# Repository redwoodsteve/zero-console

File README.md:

# Lua Console
A console which uses the RPi Zero 2 W
## setup
-Make sure to set the username and password of your pi lite image to "pi"!
-cd into `software`, and run `sudo ./setup.sh`. You should also probably turn on auto login.
## software
The folder which houses the software, such as the home screen. Basically all of this code is in C++ for a low memory footprint and stuff.<br>
**Development:**<br>
For `launcher`:
 - For windows, install MinGW64, open the UCRT64 console, CD into the launcher directory and use `make`
 - For linux, CD into the launcher directory and `make`<br>
 - Make sure to install dependencies `sudo apt install -y libgl1-mesa-dev libx11-dev libxrandr-dev libxinerama-dev libxi-dev libxcursor-dev`
 
For `games`:
 - put any files you need for any games you add in here
 - make sure to add games to `launcher/games.json`
## assets
Common assets (textures, sounds, etc) to use throughout
## hardware
The folder where you can find KiCad files, the BOM (LCSC parts) and JLCPCB files.<br>
**Development:**<br>
Probably just send suggestions as pull requests, idk how I would set up a kicad project with github like this.<br>
**Getting a PCB:**<br>
You can easily upload the `production/Zero_Console.zip` file to JLCPCB and you will be able to produce it for **$2** for five!<br>
**Parts:**<br>
You can upload the bom.csv file to LCSC and it will automatically find the parts.
For the display, [this one](https://a.co/d/03g2Kwg4) ($17) works well and is pretty cheap, but they're all the same chinese models.<br>
You'll also need some pin headers for the display and pi.<br>
And of course, you'll need a raspberry pi zero 2 w (without headers).<br>
**Assembly**<br>
Load up the PCB in kicad, and start soldering the parts to the board.

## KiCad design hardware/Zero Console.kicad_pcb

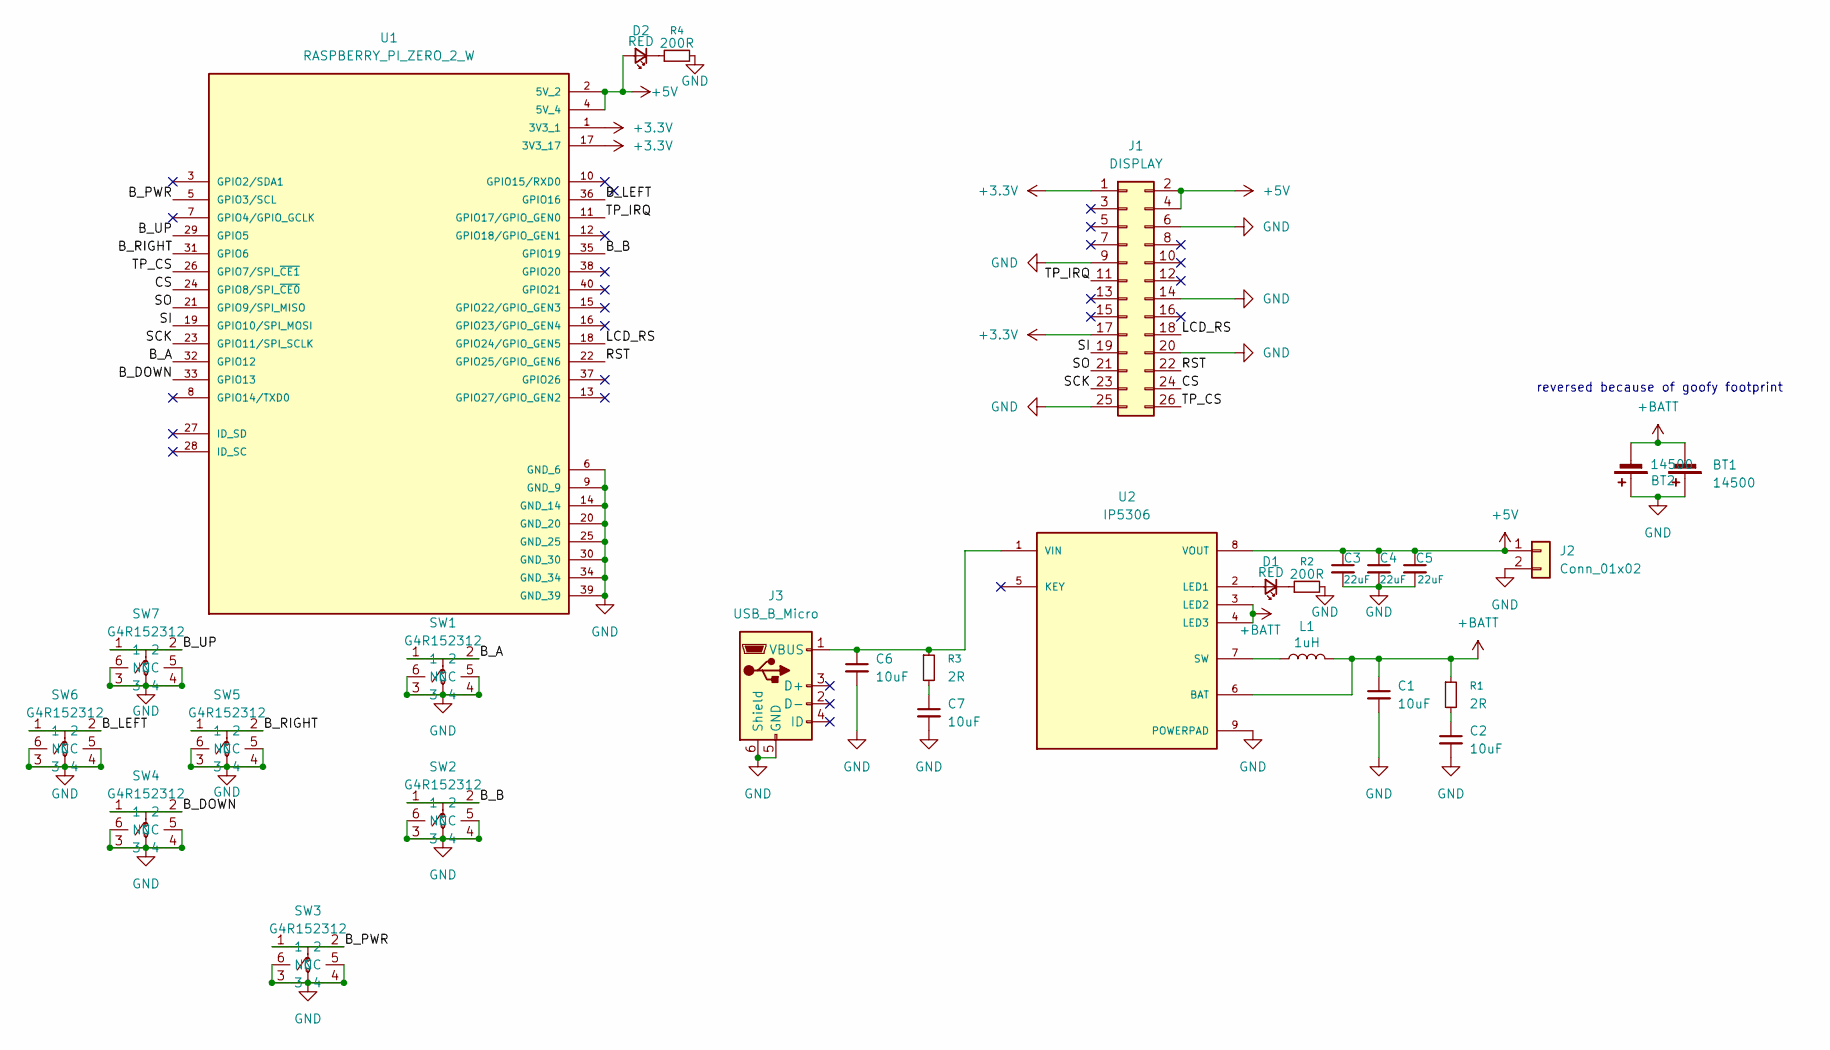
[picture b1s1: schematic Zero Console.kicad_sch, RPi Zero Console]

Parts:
BT1, BT2: 14500; BAT-TH_L56.3-W16.8-P51.55_BH-AA-A1AJ020
C1, C2, C6, C7: 10uF; C_0805_2012Metric
C3, C4, C5: 22uF; C_0805_2012Metric
D1, D2: RED; LED_0805_2012Metric
J1: DISPLAY; PinHeader_2x13_P2.54mm_Vertical
J2: Conn_01x02; PinHeader_1x02_P2.54mm_Vertical
J3: USB_B_Micro; MICRO-USB-SMD_MICROXNJ_1
L1: 1uH; IND-SMD_L4.5-W4.1_GSSM0420
R1, R3: 2R; R_0805_2012Metric
R2, R4: 200R; R_0805_2012Metric
SW1, SW2, SW3, SW4, SW5, SW6, SW7: G4R152312; SW-SMD_4P-L5.2-W5.2-P3.70-LS6.4_UK-B0233XX; LCSC Part C49393646
U1: RASPBERRY_PI_ZERO_2_W; MODULE_RASPBERRY_PI_ZERO_2_W; PARTREV April 2024
U2: IP5306; SOP127P600X165-9N; PARTREV 1.31

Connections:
+3.3V: J1.1, J1.17, U1.1 (3V3_1), U1.17 (3V3_17)
+5V: C3.1, C4.1, C5.1, D2.2 (A), J1.2, J1.4, J2.1, U1.2 (5V_2), U1.4 (5V_4), U2.8 (VOUT)
+BATT: BT1.2 (-), BT2.2 (-), C1.1, L1.2, R1.1, U2.3 (LED2), U2.4 (LED3), U2.6 (BAT)
/B_A: SW1.1, SW1.2, U1.32 (GPIO12)
/B_B: SW2.1, SW2.2, U1.35 (GPIO19)
/B_DOWN: SW4.1, SW4.2, U1.33 (GPIO13)
/B_LEFT: SW6.1, SW6.2, U1.36 (GPIO16)
/B_PWR: SW3.1, SW3.2, U1.5 (GPIO3/SCL)
/B_RIGHT: SW5.1, SW5.2, U1.31 (GPIO6)
/B_UP: SW7.1, SW7.2, U1.29 (GPIO5)
/CS: J1.24, U1.24 (GPIO8/SPI_~CE0)
/LCD_RS: J1.18, U1.18 (GPIO24/GPIO_GEN5)
/RST: J1.22, U1.22 (GPIO25/GPIO_GEN6)
/SCK: J1.23, U1.23 (GPIO11/SPI_SCLK)
/SI: J1.19, U1.19 (GPIO10/SPI_MOSI)
/SO: J1.21, U1.21 (GPIO9/SPI_MISO)
/TP_CS: J1.26, U1.26 (GPIO7/SPI_~CE1)
/TP_IRQ: J1.11, U1.11 (GPIO17/GPIO_GEN0)
GND: BT1.1 (+), BT2.1 (+), C1.2, C2.2, C3.2, C4.2, C5.2, C6.2, C7.2, J1.6, J1.9, J1.14, J1.20, J1.25, J2.2, J3.5 (GND), J3.6 (Shield), R2.2, R4.2, SW1.3, SW1.4, SW1.5 (NC), SW1.6 (NC), SW2.3, SW2.4, SW2.5 (NC), SW2.6 (NC), SW3.3, SW3.4, SW3.5 (NC), SW3.6 (NC), SW4.3, SW4.4, SW4.5 (NC), SW4.6 (NC), SW5.3, SW5.4, SW5.5 (NC), SW5.6 (NC), SW6.3, SW6.4, SW6.5 (NC), SW6.6 (NC), SW7.3, SW7.4, SW7.5 (NC), SW7.6 (NC), U1.6 (GND_6), U1.9 (GND_9), U1.14 (GND_14), U1.20 (GND_20), U1.25 (GND_25), U1.30 (GND_30), U1.34 (GND_34), U1.39 (GND_39), U2.9 (POWERPAD)
unnamed: C2.1, R1.2
unnamed: C7.1, R3.2
unnamed: D1.2 (A), U2.2 (LED1)
unnamed: D1.1 (K), R2.1
unnamed: D2.1 (K), R4.1
unnamed: C6.1, J3.1 (VBUS), R3.1, U2.1 (VIN)
unnamed: L1.1, U2.7 (SW)

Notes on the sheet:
reversed because of goofy footprint

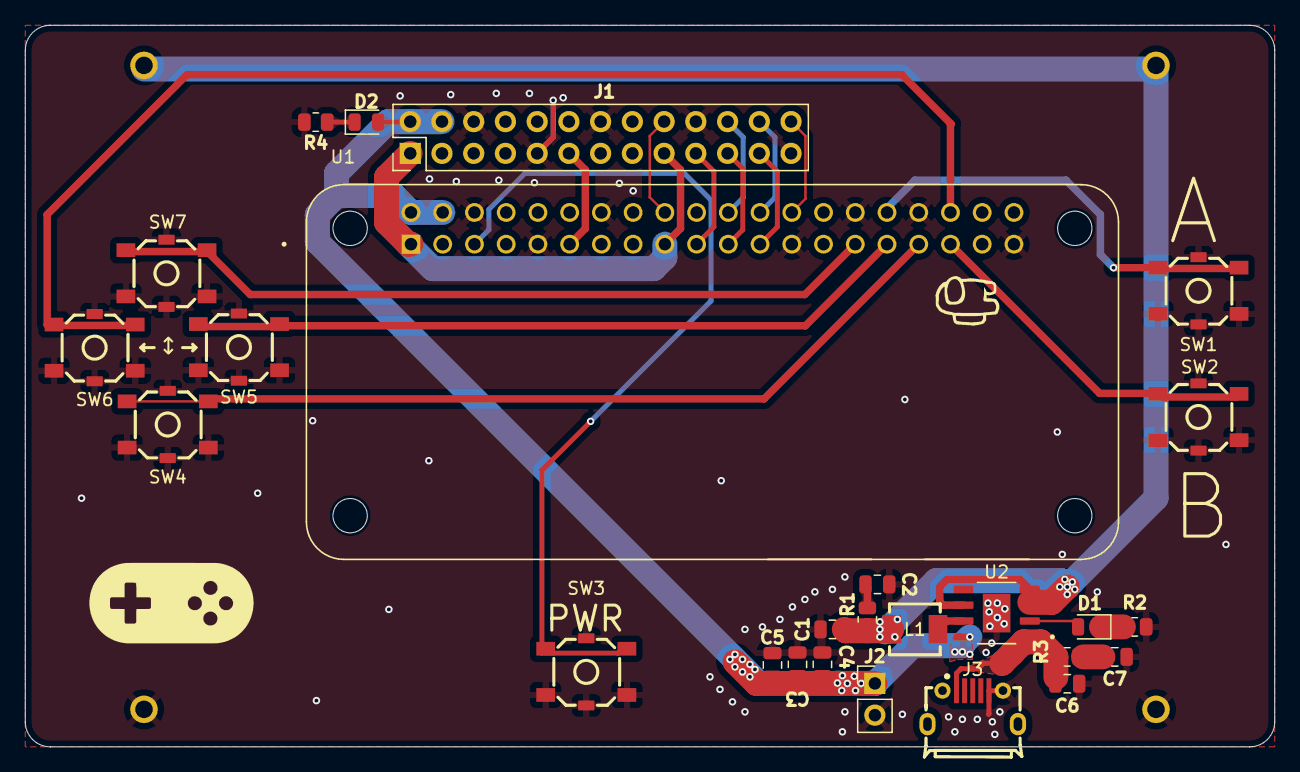
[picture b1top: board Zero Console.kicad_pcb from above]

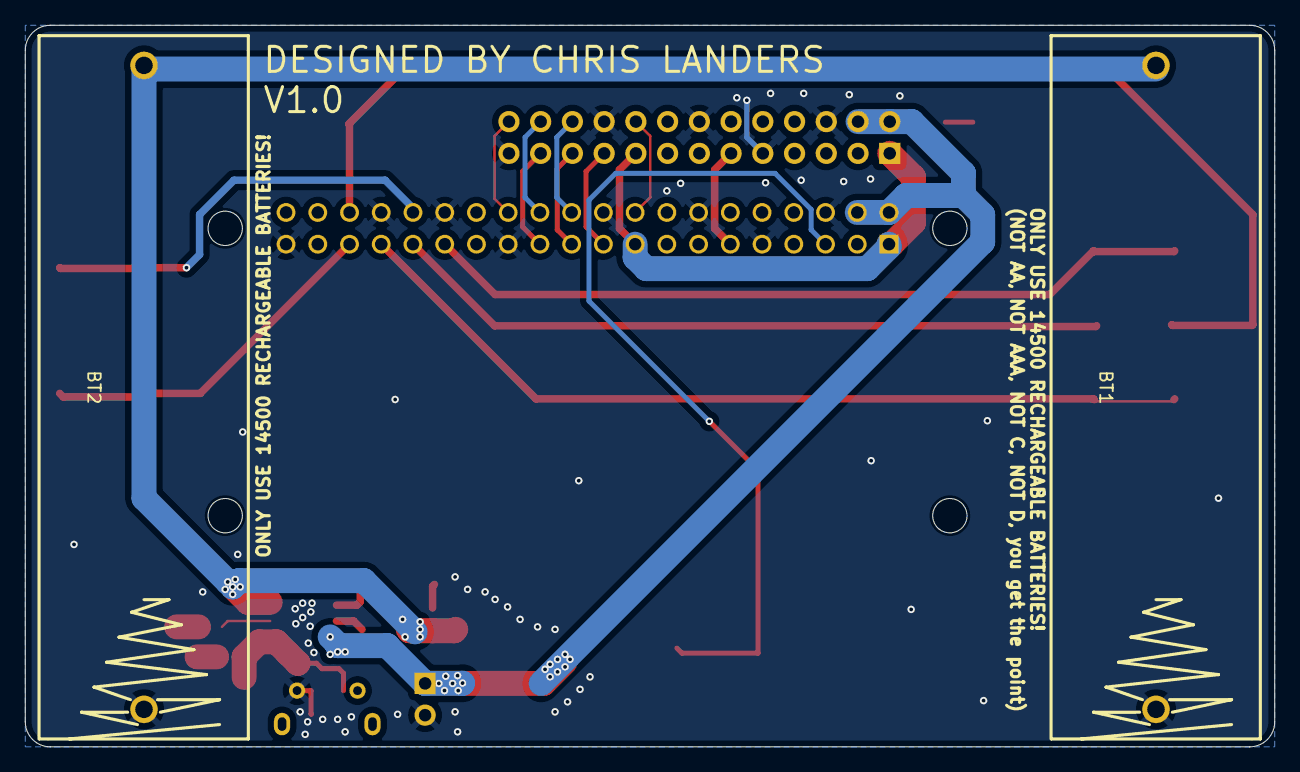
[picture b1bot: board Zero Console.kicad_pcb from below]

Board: 2 copper layers, 100.0 x 57.8 mm, 28 parts (2 on the bottom side), 26 nets.

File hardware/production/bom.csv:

Designator,Footprint,Quantity,Value,LCSC Part #
"BT1, BT2",BAT-TH_L56.3-W16.8-P51.55_BH-AA-A1AJ020,2,14500,C5290181
"C1, C2, C6, C7",0805,4,10uF,C2932476
"C3, C4, C5",0805,3,22uF,C602037
"D1, D2",0805,2,RED,C965812
J1,PinHeader_2x13_P2.54mm_Vertical,1,DISPLAY,
J2,PinHeader_1x02_P2.54mm_Vertical,1,Conn_01x02,
J3,MICRO-USB-SMD_MICROXNJ_1,1,USB_B_Micro,C404969
L1,IND-SMD_L4.5-W4.1_GSSM0420,1,1uH,C2847468
"R1, R3",0805,2,2R,C114246
"R2, R4",0805,2,200R,C17540
"SW1, SW2, SW3, SW4, SW5, SW6, SW7",SW-SMD_4P-L5.2-W5.2-P3.70-LS6.4_UK-B0233XX,7,G4R152312,C49393646
U1,MODULE_RASPBERRY_PI_ZERO_2_W,1,RASPBERRY_PI_ZERO_2_W,
U2,SOP127P600X165-9N,1,IP5306,C181692

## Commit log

2026-04-12 create all the things, including the launcher and some shared assets
2026-04-12 fix readme formattingg (add breaks)
2026-04-12 add button icons to launcher
2026-04-12 update makefile to work with linux (hopefully)
2026-04-13 make the makefile work for linux and windows, add windows prebuilt raylib
2026-04-13 add prebuilt raylib for linux (pi)
2026-04-13 add the ability to run games
2026-04-13 dont close launcher when start game, create setup script
2026-04-13 create launcher service
2026-04-17 make setup script better, create shutdown service
2026-04-17 fix setup script
2026-04-17 fix it again cuz apparently im a goober
2026-04-17 make systemd be able to open the launcher
2026-04-17 use matchbox to prevent freezing
2026-04-17 fix the launcher service, hide cursor, add design upgrade checklist (flaws.md)
2026-04-17 add blackjack game
2026-04-18 speed up display, run lfs to properly download games on setup, close the launcher when you run the game, fix the launcher selecting the wrong items
2026-04-18 make setup restart launcher and gpio shutdown services, make the launcher load quicker, add optimized version of blackjack, disable touchscreen in config.txt
